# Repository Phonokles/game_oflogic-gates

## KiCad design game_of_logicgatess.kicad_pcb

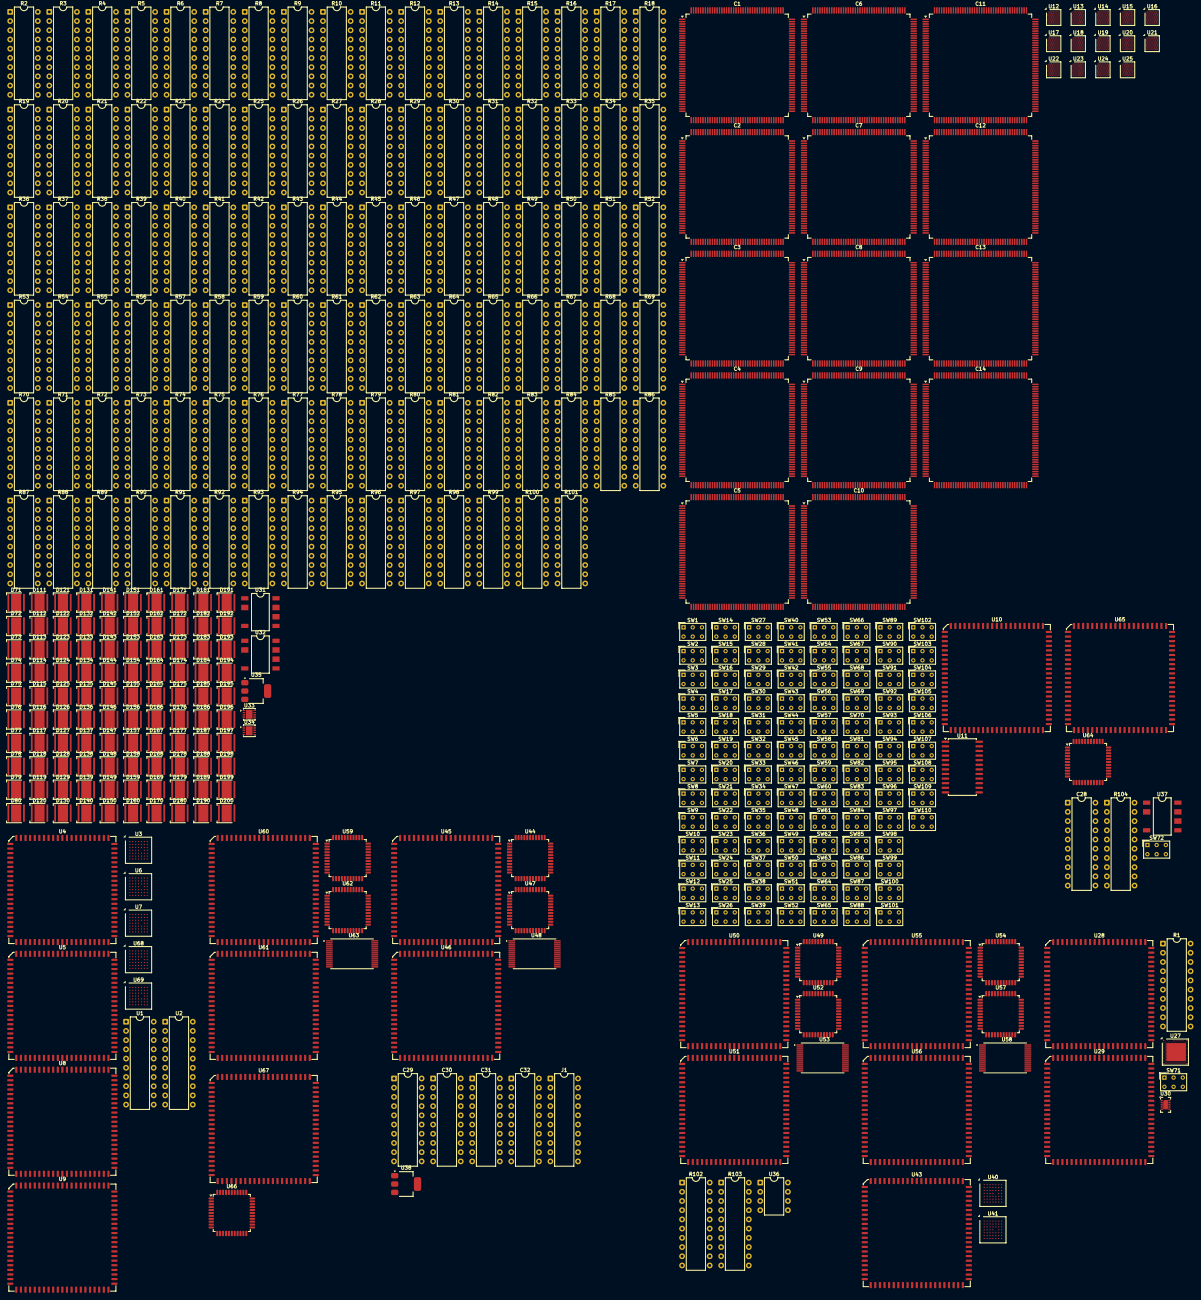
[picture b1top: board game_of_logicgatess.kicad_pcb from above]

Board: 2 copper layers, 392 parts (0 on the bottom side), 184 nets, no tracks yet.

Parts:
C1, C2, C3, C4, C5, C6, C7, C8, C9, C10, C11, C12, C13, C14: C; PQFP-160_28x28mm_P0.65mm
C28, C30, C32: 100n; DIP-20_W7.62mm
C29, C31: 10u; DIP-20_W7.62mm
D71, D72, D73, D74, D75, D76, D77, D78, D79, D80, D111, D112, D113, D114, D115, D116, D117, D118, D119, D120, D121, D122, D123, D124, D125, D126, D127, D128, D129, D130, D131, D132, D133, D134, D135, D136, D137, D138, D139, D140, D141, D142, D143, D144, D145, D146, D147, D148, D149, D150, D151, D152, D153, D154, D155, D156, D157, D158, D159, D160, D161, D162, D163, D164, D165, D166, D167, D168, D169, D170, D171, D172, D173, D174, D175, D176, D177, D178, D179, D180, D181, D182, D183, D184, D185, D186, D187, D188, D189, D190, D191, D192, D193, D194, D195, D196, D197, D198, D199, D200: LED; LED_Cree-XHP50_3V_HighDensity
J1: Conn_01x02; DIP-20_W7.62mm
R1, R102, R103, R104: 10k; DIP-20_W7.62mm
R2, R3, R4, R5, R6, R7, R8, R9, R10, R11, R12, R13, R14, R15, R16, R17, R18, R19, R20, R21, R22, R23, R24, R25, R26, R27, R28, R29, R30, R31, R32, R33, R34, R35, R36, R37, R38, R39, R40, R41, R42, R43, R44, R45, R46, R47, R48, R49, R50, R51, R52, R53, R54, R55, R56, R57, R58, R59, R60, R61, R62, R63, R64, R65, R66, R67, R68, R69, R70, R71, R72, R73, R74, R75, R76, R77, R78, R79, R80, R81, R82, R83, R84, R85, R86, R87, R88, R89, R90, R91, R92, R93, R94, R95, R96, R97, R98, R99, R100, R101: 100R; DIP-20_W7.62mm
SW1, SW2, SW3, SW4, SW5, SW6, SW7, SW8, SW9, SW10, SW11, SW12, SW13, SW14, SW15, SW16, SW17, SW18, SW19, SW20, SW21, SW22, SW23, SW24, SW25, SW26, SW27, SW28, SW29, SW30, SW31, SW32, SW33, SW34, SW35, SW36, SW37, SW38, SW39, SW40, SW41, SW42, SW43, SW44, SW45, SW46, SW47, SW48, SW49, SW50, SW51, SW52, SW53, SW54, SW55, SW56, SW57, SW58, SW59, SW60, SW61, SW62, SW63, SW64, SW65, SW66, SW67, SW68, SW69, SW70, SW71, SW72, SW81, SW82, SW83, SW84, SW85, SW86, SW87, SW88, SW89, SW90, SW91, SW92, SW93, SW94, SW95, SW96, SW97, SW98, SW99, SW100, SW101, SW102, SW103, SW104, SW105, SW106, SW107, SW108, SW109, SW110: SW_Push; SW_NKK_GW12LJP
U1, U2: 74HC192; DIP-20_W7.62mm
U3, U6, U7: 74HC02; Xilinx_CSG48_7.0x7.0mm_Layout7x7_P0.8mm
U4, U5, U8, U9, U28, U29, U43, U45, U46, U50, U51, U55, U56, U60, U61, U65, U67: 74AHC1G08; PLCC-84_29.3x29.3mm_P1.27mm
U10: 4514; PLCC-84_29.3x29.3mm_P1.27mm
U11: CD74HC4067M; SOIC-24W_7.5x15.4mm_P1.27mm
U12, U13, U14, U15, U16, U17, U18, U19, U20, U21, U22, U23, U24, U25: 74AHC273; ST_WLCSP-115_3.73x4.15mm_Layout11x21_P0.35mm_Stagger
U27: 74AHC1G02; Nordic_AQFN-94-1EP_7x7mm_P0.4mm
U30: 74AHC1G32; AMS_LGA-10-1EP_2.7x4mm_P0.6mm
U31, U32: 74HC595; PowerIntegrations_SMD-8C
U33, U34: ULN2003; WDFN-10-1EP_3x3mm_P0.5mm_EP1.8x2.5mm
U35: 4028; SOT-223
U36: NE555P; DIP-8_W7.62mm
U37: 74HC04; PowerIntegrations_SMD-8C
U38: AMS1117-3.3; SOT-223-3_TabPin2
U40: 74AHC1G02; Xilinx_CSG48_7.0x7.0mm_Layout7x7_P0.8mm
U41, U68, U69: 74AHC1G32; Xilinx_CSG48_7.0x7.0mm_Layout7x7_P0.8mm
U44, U47, U49, U52, U54, U57, U59, U62, U64, U66: 74AHC1G86; TQFP-44_10x10mm_P0.8mm
U48, U53, U58, U63: 74AHC1G32; TSOP-I-28_11.8x8mm_P0.55mm

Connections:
+3V3: C1.1, C2.2, C3.2, C4.2, C5.1, C6.1, C7.1, C8.1, C9.1, C10.1, C11.1, C12.1, C13.1, C14.1, C29.1, C32.1, R102.1, R104.1, SW71.1, U1.4 (DOWN), U1.11 (~LOAD), U1.16 (VCC), U2.4 (DOWN), U2.11 (~LOAD), U2.16 (VCC), U4.5 (VCC), U5.5 (VCC), U8.5 (VCC), U9.5 (VCC), U10.1 (EL), U10.24 (Vdd), U11.24 (VCC), U28.5 (VCC), U29.5 (VCC), U30.5 (VCC), U36.4 (~RST), U36.8 (VCC), U38.2 (VO), U44.5 (VCC), U45.5 (VCC), U46.5 (VCC), U47.5 (VCC), U49.5 (VCC), U50.5 (VCC), U51.5 (VCC), U52.5 (VCC), U54.5 (VCC), U55.5 (VCC), U56.5 (VCC), U57.5 (VCC), U59.5 (VCC), U60.5 (VCC), U61.5 (VCC), U62.5 (VCC), U64.5 (VCC), U65.5 (VCC), U66.5 (VCC), U67.5 (VCC)
+5V: C30.1, C31.1, J1.1, U38.3 (VI)
/calculator/b1: U43.2, U66.4
/calculator/c1: U48.4, U59.1, U60.1
/calculator/c2: U53.4, U59.2, U60.2
/calculator/c3: U61.2, U62.2, U65.4
/calculator/c4: U58.4, U66.1, U67.1
/calculator/s1: U47.4, U54.1, U55.1
/calculator/s2: U52.4, U54.2, U55.2
/calculator/s3: U56.2, U57.2, U64.4
/calculator/s5: U62.4, U66.2, U67.2
CLEAR: C28.1, R104.2, U1.14 (CLR), U2.14 (CLR), U37.1
CLK: U1.5 (UP), U36.3 (OUT)
DSPALTE0: R2.2, R12.2, R22.2, R32.2, R42.2, R52.2, R62.2, R72.2, R82.2, R92.2
DSPALTE1: R3.2, R13.2, R23.2, R33.2, R43.2, R53.2, R63.2, R73.2, R83.2, R93.2, U31.1 (QB)
DSPALTE2: R4.2, R14.2, R24.2, R34.2, R44.2, R54.2, R64.2, R74.2, R84.2, R94.2, U31.2 (QC)
DSPALTE3: R5.2, R15.2, R25.2, R35.2, R45.2, R55.2, R65.2, R75.2, R85.2, R95.2
DSPALTE4: R6.2, R16.2, R26.2, R36.2, R46.2, R56.2, R66.2, R76.2, R86.2, R96.2, U31.4 (QE)
DSPALTE5: R7.2, R17.2, R27.2, R37.2, R47.2, R57.2, R67.2, R77.2, R87.2, R97.2, U31.5 (QF)
DSPALTE6: R8.2, R18.2, R28.2, R38.2, R48.2, R58.2, R68.2, R78.2, R88.2, R98.2, U31.6 (QG)
DSPALTE7: R9.2, R19.2, R29.2, R39.2, R49.2, R59.2, R69.2, R79.2, R89.2, R99.2, U31.7 (QH)
DSPALTE8: R10.2, R20.2, R30.2, R40.2, R50.2, R60.2, R70.2, R80.2, R90.2, R100.2
DSPALTE9: R11.2, R21.2, R31.2, R41.2, R51.2, R61.2, R71.2, R81.2, R91.2, R101.2
DZEILE0: U33.1 (I1), U35.3 (S0)
DZEILE2: U33.3 (I3), U35.2 (S2)
DZEILE4: U33.5 (I5), U35.1 (S4)
DZEILE7: U34.3 (I3), U35.4 (S7)
GND: C1.2, C2.1, C3.1, C4.1, C5.2, C6.2, C7.2, C8.2, C10.2, C11.2, C12.2, C13.2, C14.2, C29.2, C30.2, C31.2, C32.2, J1.2, R1.2, SW72.2, U1.1 (B), U1.8 (GND), U1.9 (D), U1.10 (C), U1.15 (A), U2.1 (B), U2.8 (GND), U2.9 (D), U2.10 (C), U2.15 (A), U4.3 (GND), U5.3 (GND), U8.3 (GND), U9.3 (GND), U10.12 (Vss), U10.23 (~EN), U11.12 (GND), U11.15 (~E), U28.3 (GND), U29.3 (GND), U30.3 (GND), U36.1 (GND), U38.1 (GND), U43.3 (GND), U44.3 (GND), U45.3 (GND), U46.3 (GND), U47.3 (GND), U48.3 (GND), U49.3 (GND), U50.3 (GND), U51.3 (GND), U52.3 (GND), U53.3 (GND), U54.3 (GND), U55.3 (GND), U56.3 (GND), U57.3 (GND), U58.3 (GND), U59.3 (GND), U60.3 (GND), U61.3 (GND), U62.3 (GND), U63.3 (GND), U64.3 (GND), U65.3 (GND), U66.3 (GND), U67.3 (GND)
MZEILE0: D141.1 (K), D142.1 (K), D143.1 (K), D144.1 (K), D145.1 (K), D146.1 (K), D147.1 (K), D148.1 (K), D149.1 (K), D150.1 (K)
MZEILE1: D151.1 (K), D152.1 (K), D153.1 (K), D154.1 (K), D155.1 (K), D156.1 (K), D157.1 (K), D158.1 (K), D159.1 (K), D160.1 (K)
MZEILE2: D71.1 (K), D72.1 (K), D73.1 (K), D74.1 (K), D75.1 (K), D76.1 (K), D77.1 (K), D78.1 (K), D79.1 (K), D80.1 (K)
MZEILE3: D111.1 (K), D112.1 (K), D113.1 (K), D114.1 (K), D115.1 (K), D116.1 (K), D117.1 (K), D118.1 (K), D119.1 (K), D120.1 (K)
MZEILE4: D121.1 (K), D122.1 (K), D123.1 (K), D124.1 (K), D125.1 (K), D126.1 (K), D127.1 (K), D128.1 (K), D129.1 (K), D130.1 (K)
MZEILE5: D131.1 (K), D132.1 (K), D133.1 (K), D134.1 (K), D135.1 (K), D136.1 (K), D137.1 (K), D138.1 (K), D139.1 (K), D140.1 (K)
MZEILE6: D161.1 (K), D162.1 (K), D163.1 (K), D164.1 (K), D165.1 (K), D166.1 (K), D167.1 (K), D168.1 (K), D169.1 (K), D170.1 (K)
MZEILE7: D171.1 (K), D172.1 (K), D173.1 (K), D174.1 (K), D175.1 (K), D176.1 (K), D177.1 (K), D178.1 (K), D179.1 (K), D180.1 (K)
MZEILE8: D181.1 (K), D182.1 (K), D183.1 (K), D184.1 (K), D185.1 (K), D186.1 (K), D187.1 (K), D188.1 (K), D189.1 (K), D190.1 (K)
MZEILE9: D191.1 (K), D192.1 (K), D193.1 (K), D194.1 (K), D195.1 (K), D196.1 (K), D197.1 (K), D198.1 (K), D199.1 (K), D200.1 (K)
N0: U44.1, U45.1
N1: U44.2, U45.2
N2: U46.2, U47.2
N3: U49.1, U50.1
N4: U49.2, U50.2
N5: U51.2, U52.2
N6: U64.1, U65.1
N7: U64.2, U65.2
unnamed: C28.2, SW72.1
unnamed: D71.2 (A), R2.1
unnamed: D72.2 (A), R3.1
unnamed: D73.2 (A), R4.1
unnamed: D74.2 (A), R5.1
unnamed: D75.2 (A), R6.1
unnamed: D76.2 (A), R7.1
unnamed: D77.2 (A), R8.1
unnamed: D78.2 (A), R9.1
unnamed: D79.2 (A), R10.1
unnamed: D80.2 (A), R11.1
unnamed: D111.2 (A), R12.1
unnamed: D112.2 (A), R13.1
unnamed: D113.2 (A), R14.1
unnamed: D114.2 (A), R15.1
unnamed: D115.2 (A), R16.1
unnamed: D116.2 (A), R17.1
unnamed: D117.2 (A), R18.1
unnamed: D118.2 (A), R19.1
unnamed: D119.2 (A), R20.1
unnamed: D120.2 (A), R21.1
unnamed: D121.2 (A), R22.1
unnamed: D122.2 (A), R23.1
unnamed: D123.2 (A), R24.1
unnamed: D124.2 (A), R25.1
unnamed: D125.2 (A), R26.1
unnamed: D126.2 (A), R27.1
unnamed: D127.2 (A), R28.1
unnamed: D128.2 (A), R29.1
unnamed: D129.2 (A), R30.1
unnamed: D130.2 (A), R31.1
unnamed: D131.2 (A), R32.1
unnamed: D132.2 (A), R33.1
unnamed: D133.2 (A), R34.1
unnamed: D134.2 (A), R35.1
unnamed: D135.2 (A), R36.1
unnamed: D136.2 (A), R37.1
unnamed: D137.2 (A), R38.1
unnamed: D138.2 (A), R39.1
unnamed: D139.2 (A), R40.1
unnamed: D140.2 (A), R41.1
unnamed: D141.2 (A), R42.1
unnamed: D142.2 (A), R43.1
unnamed: D143.2 (A), R44.1
unnamed: D144.2 (A), R45.1
unnamed: D145.2 (A), R46.1
unnamed: D146.2 (A), R47.1
unnamed: D147.2 (A), R48.1
unnamed: D148.2 (A), R49.1
unnamed: D149.2 (A), R50.1
unnamed: D150.2 (A), R51.1
unnamed: D151.2 (A), R52.1
unnamed: D152.2 (A), R53.1
unnamed: D153.2 (A), R54.1
unnamed: D154.2 (A), R55.1
unnamed: D155.2 (A), R56.1
unnamed: D156.2 (A), R57.1
unnamed: D157.2 (A), R58.1
unnamed: D158.2 (A), R59.1
unnamed: D159.2 (A), R60.1
unnamed: D160.2 (A), R61.1
unnamed: D161.2 (A), R62.1
unnamed: D162.2 (A), R63.1
unnamed: D163.2 (A), R64.1
unnamed: D164.2 (A), R65.1
unnamed: D165.2 (A), R66.1
unnamed: D166.2 (A), R67.1
unnamed: D167.2 (A), R68.1
unnamed: D168.2 (A), R69.1
unnamed: D169.2 (A), R70.1
unnamed: D170.2 (A), R71.1
unnamed: D171.2 (A), R72.1
unnamed: D172.2 (A), R73.1
unnamed: D173.2 (A), R74.1
unnamed: D174.2 (A), R75.1
unnamed: D175.2 (A), R76.1
unnamed: D176.2 (A), R77.1
unnamed: D177.2 (A), R78.1
unnamed: D178.2 (A), R79.1
unnamed: D179.2 (A), R80.1
unnamed: D180.2 (A), R81.1
unnamed: D181.2 (A), R82.1
unnamed: D182.2 (A), R83.1
unnamed: D183.2 (A), R84.1
unnamed: D184.2 (A), R85.1
unnamed: D185.2 (A), R86.1
unnamed: D186.2 (A), R87.1
unnamed: D187.2 (A), R88.1
unnamed: D188.2 (A), R89.1
unnamed: D189.2 (A), R90.1
unnamed: D190.2 (A), R91.1
unnamed: D191.2 (A), R92.1
unnamed: D192.2 (A), R93.1
unnamed: D193.2 (A), R94.1
unnamed: D194.2 (A), R95.1
unnamed: D195.2 (A), R96.1
unnamed: D196.2 (A), R97.1
unnamed: D197.2 (A), R98.1
unnamed: D198.2 (A), R99.1
unnamed: D199.2 (A), R100.1
unnamed: D200.2 (A), R101.1
unnamed: R102.2, R103.1, U36.7 (DISCH)
unnamed: R103.2, U36.2 (TRIG), U36.6 (THRES)
unnamed: U44.4, U47.1
unnamed: U45.4, U48.1
unnamed: U46.4, U48.2
unnamed: U49.4, U52.1
unnamed: U50.4, U53.1
unnamed: U51.4, U53.2
unnamed: U54.4, U57.1
unnamed: U55.4, U58.1
unnamed: U56.4, U58.2
unnamed: U59.4, U62.1
unnamed: U60.4, U63.1
unnamed: U61.4, U63.2
RUN_TASTER: R1.1, SW71.2
SP0: U8.1, U11.10 (S0)
SP1: U1.2 (QB), U1.3 (QA), U11.11 (S1)
SP2: U1.6 (QC), U11.14 (S2)
SP3: U1.7 (QD), U8.2, U11.13 (S3)
SP_UEBERLAUF_N: U1.12 (~CO), U2.5 (UP)
TASTE_AKTIV: U11.1 (COM), U29.1
TEMP_A: U28.4, U30.2
TEMP_B: U29.4, U30.1
TZEILE0: SW1.1, SW11.1, SW21.1, SW31.1, SW41.1, SW51.1, SW61.1, SW81.1, SW91.1, SW101.1, U10.11 (Q0)
TZEILE1: SW2.1, SW12.1, SW22.1, SW32.1, SW42.1, SW52.1, SW62.1, SW82.1, SW92.1, SW102.1, U10.9 (Q1)
TZEILE2: SW3.1, SW13.1, SW23.1, SW33.1, SW43.1, SW53.1, SW63.1, SW83.1, SW93.1, SW103.1, U10.10 (Q2)
TZEILE3: SW4.1, SW14.1, SW24.1, SW34.1, SW44.1, SW54.1, SW64.1, SW84.1, SW94.1, SW104.1, U10.8 (Q3)
TZEILE4: SW5.1, SW15.1, SW25.1, SW35.1, SW45.1, SW55.1, SW65.1, SW85.1, SW95.1, SW105.1, U10.7 (Q4)
TZEILE5: SW6.1, SW16.1, SW26.1, SW36.1, SW46.1, SW56.1, SW66.1, SW86.1, SW96.1, SW106.1, U10.6 (Q5)
TZEILE6: SW7.1, SW17.1, SW27.1, SW37.1, SW47.1, SW57.1, SW67.1, SW87.1, SW97.1, SW107.1, U10.5 (Q6)
TZEILE7: SW8.1, SW18.1, SW28.1, SW38.1, SW48.1, SW58.1, SW68.1, SW88.1, SW98.1, SW108.1, U10.4 (Q7)
TZEILE8: SW9.1, SW19.1, SW29.1, SW39.1, SW49.1, SW59.1, SW69.1, SW89.1, SW99.1, SW109.1, U10.18 (Q8)
TZEILE9: SW10.1, SW20.1, SW30.1, SW40.1, SW50.1, SW60.1, SW70.1, SW90.1, U10.17 (Q9)
ZL0: U2.3 (QA), U5.1, U10.2 (A0)
ZL1: U2.2 (QB), U10.3 (A1)
ZL2: U2.6 (QC), U10.21 (A2)
ZL3: U2.7 (QD), U5.2, U10.22 (A3)
